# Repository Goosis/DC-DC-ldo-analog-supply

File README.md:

#  Dual-Stage Power Supply (DC-DC Buck + LDO)

**Input:** 6–10V DC  
**Output 1:** 4V @ 3.5A (Buck Converter)  
**Output 2:** 2.6V @ 1.7A (LDO Regulator)  
**Design Tool:** KiCad  
**ICs:** TPS56837H (Buck), TPS7A53B (LDO)

---

##  Description

This is a compact, efficient two-stage power supply designed for low-noise and high-current applications. It converts a 6–10V DC input into:

- 4V @ 3.5A via DC-DC Buck (TPS56837H)
- 2.6V @ 1.7A via LDO (TPS7A53B)

The design was based on official **Texas Instruments datasheets**, simulation tools, and PCB manufacturer guidelines. Great care was taken in layout, thermal management, and ground isolation.

---

##  Key Components

| Stage | IC           | Vin         | Vout | Iout Max | Notes                        |
|-------|--------------|-------------|------|----------|------------------------------|
| Buck  | TPS56837H    | 6–10 V      | 4 V  | 3.5 A    | Synchronous, 500 kHz         |
| LDO   | TPS7A53B     | 4 V         | 2.6 V| 1.7 A    | Ultra-low noise, high PSRR   |

---

##  Layout Design vs TI Recommendation

This PCB layout was designed by following layout principles from the **TPS56837H datasheet**.

<table>
  <tr>
    <td><b>TI Recommended Layout</b><br/></td>
    <td><b>My PCB Layout (KiCad)</b><br/></td>
  </tr>
</table>

 **Matched Design Features:**
- Short loops for high-current paths (Cin → SW → Inductor → Cout)
- Correct placement of decoupling capacitors near IC pins
- AGND and PGND separation via internal planes and via stitching
- Wide copper traces sized according to 3.5A requirement
- Respect of layout zones for analog feedback and control

---
---

##  PSpice Simulation

The design was simulated in PSpice using vendor-provided models for both the buck converter (TPS56837H) and LDO (TPS7A5301).  
This helped verify soft-start behavior, regulation stability, and output timing before fabrication.

<table>
  <tr>
    <td><b>Schematic (PSpice)</b><br/></td>
    <td><b>Simulation Result</b><br/></td>
  </tr>
</table>

Green = Vout1 (4 V)  
Red = Vout2 (2.6 V)

The simulation shows proper soft-start ramp-up and sequential regulation, matching expectations.

Simulation files are aviable on my [Google Drive](https://drive.google.com/drive/folders/1zhOBsbE7j7mKasGqCcKV4JfBKCOTLMK9?hl=cs)

##  Images

### Schematic  

### PCB Layout (Top Layer)  

### 3D View  

---

## ⚠️ Design Challenges & Fixes

###  LDO BIAS Pin Not Connected

In the first revision, the **BIAS pin** of the LDO (TPS7A53B) was left floating.  
According to [section 8.3.1.2 of the datasheet](https://www.ti.com/lit/ds/symlink/tps7a53b.pdf#page=19), this causes the output to **follow the input voltage** instead of regulating — which is exactly what happened.

📌 **Fix:** Connected BIAS to VIN (4 V) and added a 1 µF capacitor to GND, as recommended in the datasheet.

---

###  Incorrect EN Pin Logic on Buck Converter

Initially, the **EN pin** of the buck converter was connected to its own output (VOUT), assuming it would enable itself after power-up.  
However, this caused the converter to stay disabled at startup.

📌 **Fix:** Connected EN to VIN through a **resistor divider**, ensuring a valid logic-high signal at startup. This resolved the issue and allowed proper converter initialization.

---

###  TI-Provided Footprint Had Pad Issues

The **footprint from TI's UltraLibrarian export** for the TPS7A53B had issues:
- Some **pads were incorrectly shaped or numbered**
- **Routing was blocked** due to KiCad DRC violations

📌 **Fix:** Manually edited the footprint in **KiCad Footprint Editor** to:
- Adjust pad shapes and positions
- Fix pin numbering
- Ensure proper copper connection and DRC clearance

---

These issues were identified during layout review and early testing, and fixed in preparation for the next board revision.

---

##  Project Files

- `/schematic/` — KiCad schematic (`.kicad_sch`)  
- `/pcb/` — KiCad board layout (`.kicad_pcb`)  
- `/gerbers/` — Gerber files for fabrication  
- `/bom/` — Bill of Materials  
- `/pdf/` — PDF exports of schematic and layout

---

##  Tools & Calculators Used

- [TI Webench Power Designer](https://webench.ti.com/power-designer/)
- [ChipDip Voltage Divider Calculator](https://www.chipdip.ru/calc/voltage-divider)
- [Trace Width Calculator (AdvancedPCB)](https://www.advancedpcb.com/en-us/tools/trace-width-calculator/)
- [Via Properties Calculator (911EDA)](https://www.911eda.com/pcb-design-calculators/via-properties-calculator/)
- [JLCPCB Capabilities](https://jlcpcb.com/capabilities/pcb-capabilities)

---

## ✅ Project Status

- [x] Schematic complete  
- [x] PCB layout finished  
- [x] BOM generated  
- [x] Layout verified vs datasheet  
- [ ] PCB ordered  
- [ ] Load testing  
- [ ] Ripple and thermal validation

---

## 📚 References

- [TPS56837H Datasheet](https://www.ti.com/product/TPS56837H)
- [TPS7A53B Datasheet](https://www.ti.com/product/TPS7A53B)
- [KiCad Docs](https://docs.kicad.org/)

---

> 💬 Suggestions, improvements, or critiques are welcome. This design is still open for review.

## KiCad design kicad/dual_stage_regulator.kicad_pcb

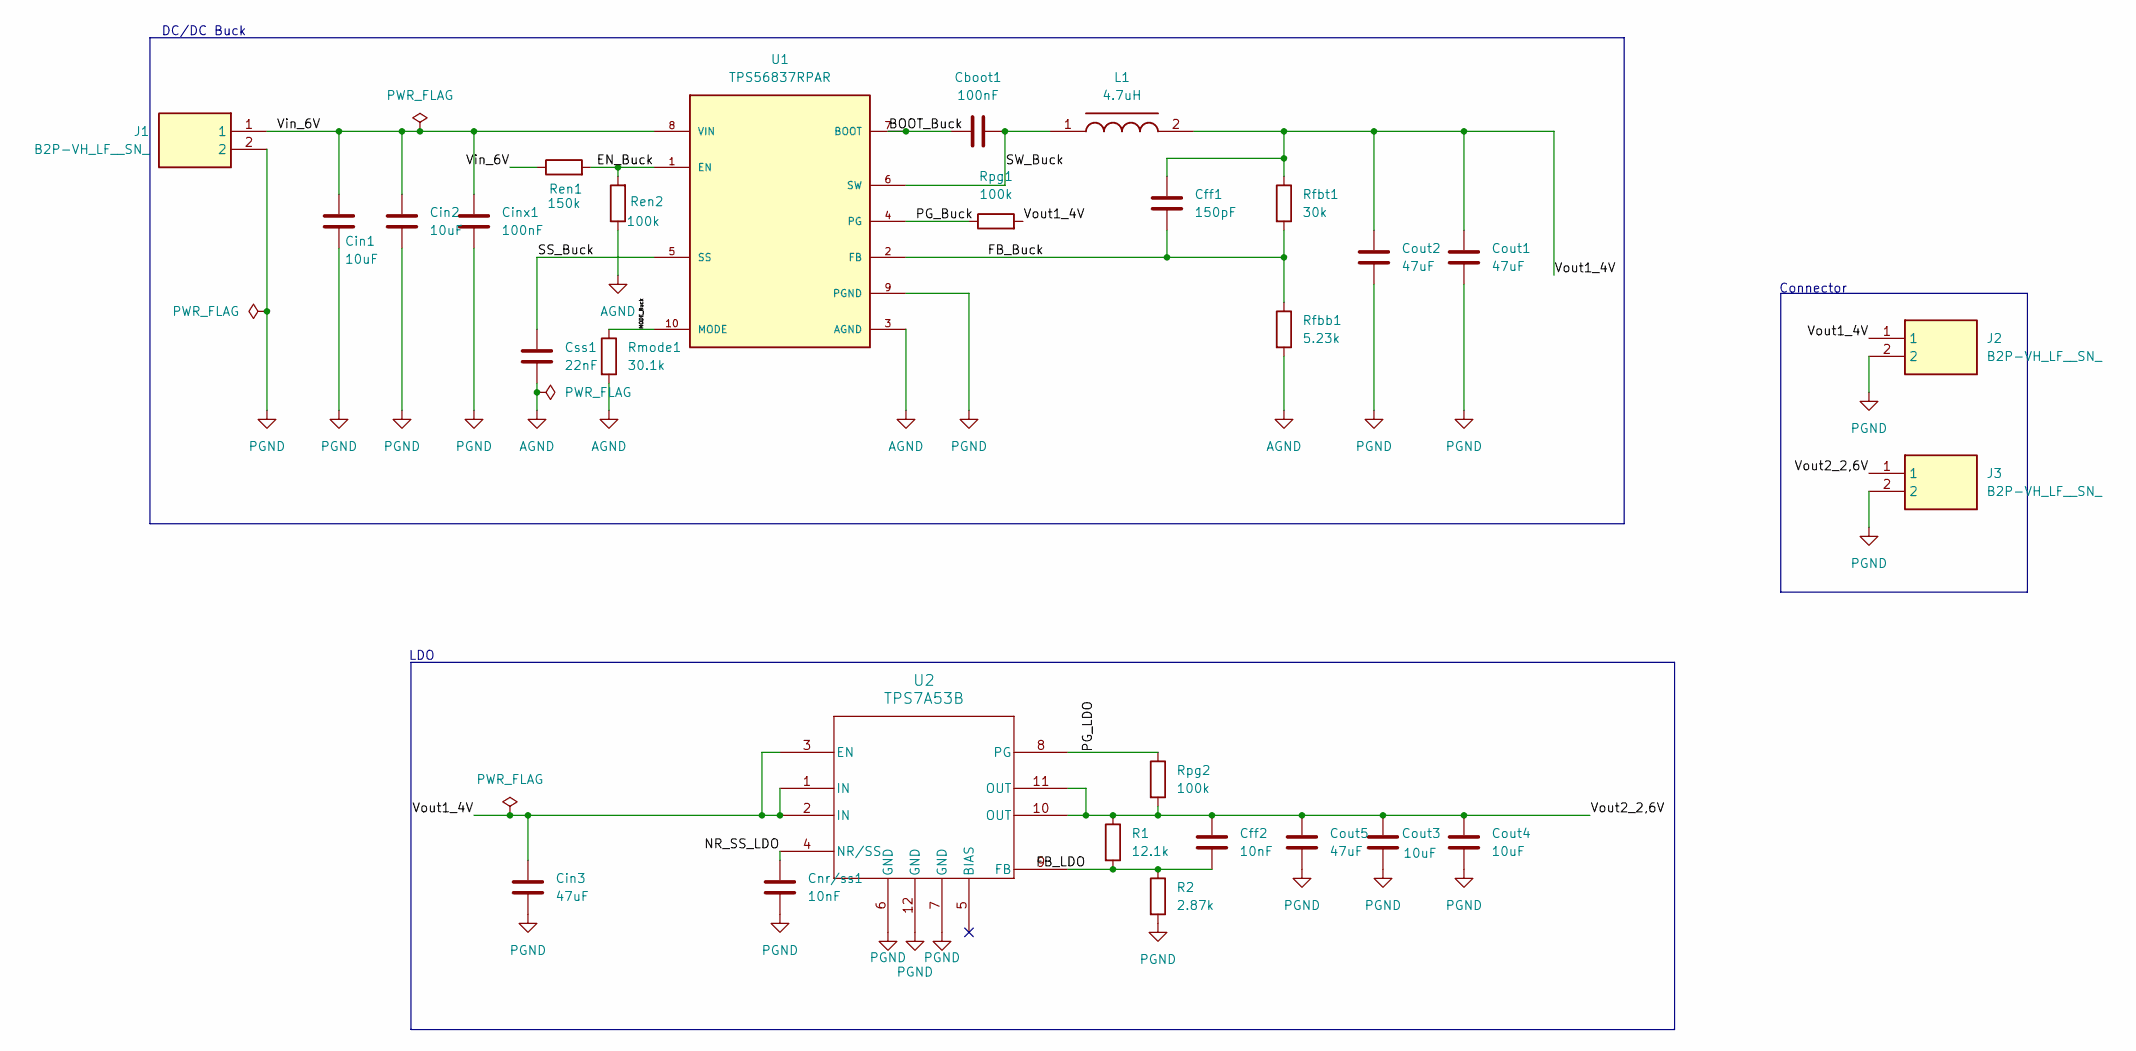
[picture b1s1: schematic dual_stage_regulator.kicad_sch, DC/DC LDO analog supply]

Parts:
Cboot1: 100nF; C_0603_1608Metric
Cff1: 150pF; C_0201_0603Metric
Cff2: 10nF; C_0402_1005Metric
Cin1, Cin2: 10uF; C_0805_2012Metric
Cin3: 47uF; R_0805_2012Metric
Cinx1: 100nF; C_0805_2012Metric
Cnr/ss1: 10nF; C_0402_1005Metric
Cout1, Cout2: 47uF; C_1206_3216Metric
Cout3, Cout4: 10uF; R_0805_2012Metric
Cout5: 47uF; R_0805_2012Metric
Css1: 22nF; C_0402_1005Metric
J1, J2, J3: B2P-VH_LF__SN_; SHDR2W155P0X396_1X2_777X1001X1184P; Mouser Part Number N/A
L1: 4.7uH; SPM6530; Mouser Part Number 810-SPM6530T-4R7M
R1: 12.1k; R_0402_1005Metric
R2: 2.87k; R_0402_1005Metric
Ren1: 150k; R_0402_1005Metric
Ren2: 100k; R_0402_1005Metric
Rfbb1: 5.23k; R_0402_1005Metric
Rfbt1: 30k; R_0603_1608Metric
Rmode1: 30.1k; R_0805_2012Metric
Rpg1, Rpg2: 100k; R_0402_1005Metric
U1: TPS56837RPAR; CONV_TPS56837RPAR; PARTREV A
U2: TPS7A53B; VQFN-HR12_RPS_TEX

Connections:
/BOOT_Buck: Cboot1.1, U1.7 (BOOT); also elsewhere on the board
/EN_Buck: Ren1.2, Ren2.2, U1.1 (EN); also elsewhere on the board
/FB_Buck: Cff1.2, Rfbb1.1, Rfbt1.2, U1.2 (FB); also elsewhere on the board
/FB_LDO: Cff2.2, R1.2, R2.1, U2.9 (FB); also elsewhere on the board
/MODE_Buck: Rmode1.1, U1.10 (MODE); also elsewhere on the board
/NR_SS_LDO: Cnr/ss1.1, U2.4 (NR/SS); also elsewhere on the board
/PG_Buck: Rpg1.1, U1.4 (PG); also elsewhere on the board
/PG_LDO: Rpg2.1, U2.8 (PG); also elsewhere on the board
/SS_Buck: Css1.1, U1.5 (SS); also elsewhere on the board
/SW_Buck: Cboot1.2, L1.1, U1.6 (SW); also elsewhere on the board
/Vin_6V: Cin1.1, Cin2.1, Cinx1.1, J1.1, Ren1.1, U1.8 (VIN); also elsewhere on the board
/Vout1_4V: Cff1.1, Cin3.1, Cout1.1, Cout2.1, J2.1, L1.2, Rfbt1.1, Rpg1.2, U2.1 (IN), U2.2 (IN), U2.3 (EN); also elsewhere on the board
/Vout2_2,6V: Cff2.1, Cout3.1, Cout4.1, Cout5.1, J3.1, R1.1, Rpg2.2, U2.10 (OUT), U2.11 (OUT); also elsewhere on the board
AGND: Css1.2, Ren2.1, Rfbb1.2, Rmode1.2, U1.3 (AGND); also elsewhere on the board
PGND: Cin1.2, Cin2.2, Cin3.2, Cinx1.2, Cnr/ss1.2, Cout1.2, Cout2.2, Cout3.2, Cout4.2, Cout5.2, J1.2, J2.2, J3.2, R2.2, U1.9 (PGND), U2.6 (GND), U2.7 (GND), U2.12 (GND); also elsewhere on the board

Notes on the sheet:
DC/DC Buck
LDO
Connector

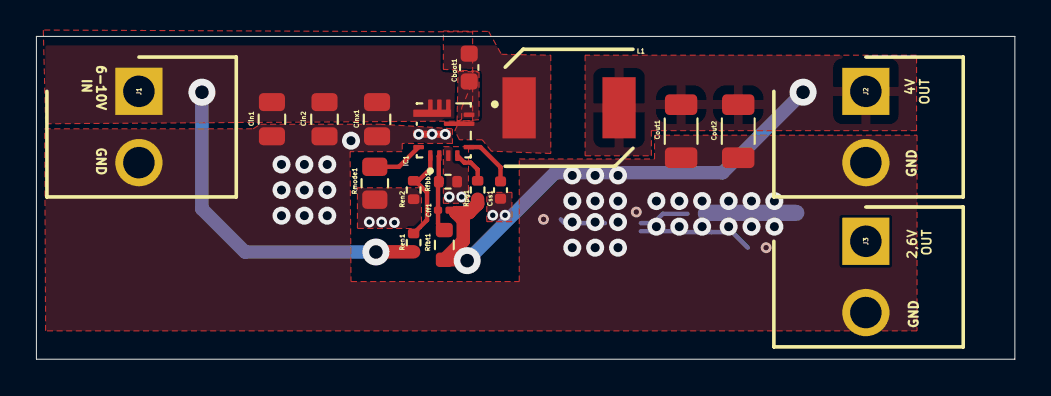
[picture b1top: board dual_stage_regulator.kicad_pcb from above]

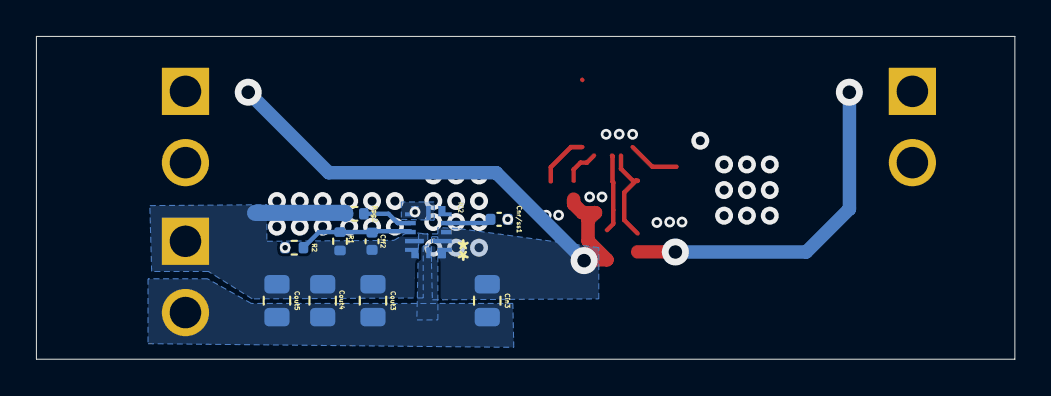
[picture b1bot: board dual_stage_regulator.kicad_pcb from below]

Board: 4 copper layers, 54.4 x 17.9 mm, 29 parts (10 on the bottom side), 15 nets.

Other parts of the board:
IC1: TPS56837RPAR; CONV_TPS56837RPAR
IC2: TPS7A53B; VQFN-HR12_RPS_TEX

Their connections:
/BOOT_Buck: IC1.7 (BOOT); also elsewhere on the board
/EN_Buck: IC1.1 (EN); also elsewhere on the board
/FB_Buck: IC1.2 (FB); also elsewhere on the board
/FB_LDO: IC2.9 (FB); also elsewhere on the board
/MODE_Buck: IC1.10 (MODE); also elsewhere on the board
/NR_SS_LDO: IC2.4 (NR/SS); also elsewhere on the board
/PG_Buck: IC1.4 (PG); also elsewhere on the board
/PG_LDO: IC2.8 (PG); also elsewhere on the board
/SS_Buck: IC1.5 (SS); also elsewhere on the board
/SW_Buck: IC1.6 (SW); also elsewhere on the board
/Vin_6V: IC1.8 (VIN); also elsewhere on the board
/Vout1_4V: IC2.1 (IN), IC2.2 (IN), IC2.3 (EN); also elsewhere on the board
/Vout2_2,6V: IC2.10 (OUT), IC2.11 (OUT); also elsewhere on the board
AGND: IC1.3 (AGND); also elsewhere on the board
PGND: IC1.9 (PGND), IC2.6 (GND), IC2.7 (GND), IC2.12 (GND); also elsewhere on the board

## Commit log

2025-04-08 Rename img/Screenshot 2025-04-08 at 15.56.57.png to PCB_top.png
2025-04-08 Rename PCB_top.png to img/PCB_top.png
2025-04-08 Create gitignore
2025-04-08 Create d
2025-04-09 Create simulation
